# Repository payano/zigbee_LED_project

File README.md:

# zigbee_LED_project

Inspiration:
https://arduinodiy.wordpress.com/2012/05/02/using-mosfets-with-ttl-levels/

this aswell: https://github.com/karlp/Mrf24j40-arduino-library/

Potentiometer
BC547
IRF3205
LED-panel (aliexpress)
RGBW-led strips (aliexpress)

THIS TOO: https://electronics.stackexchange.com/questions/132000/stm32-series-microcontroller-calculations-of-timer-variables

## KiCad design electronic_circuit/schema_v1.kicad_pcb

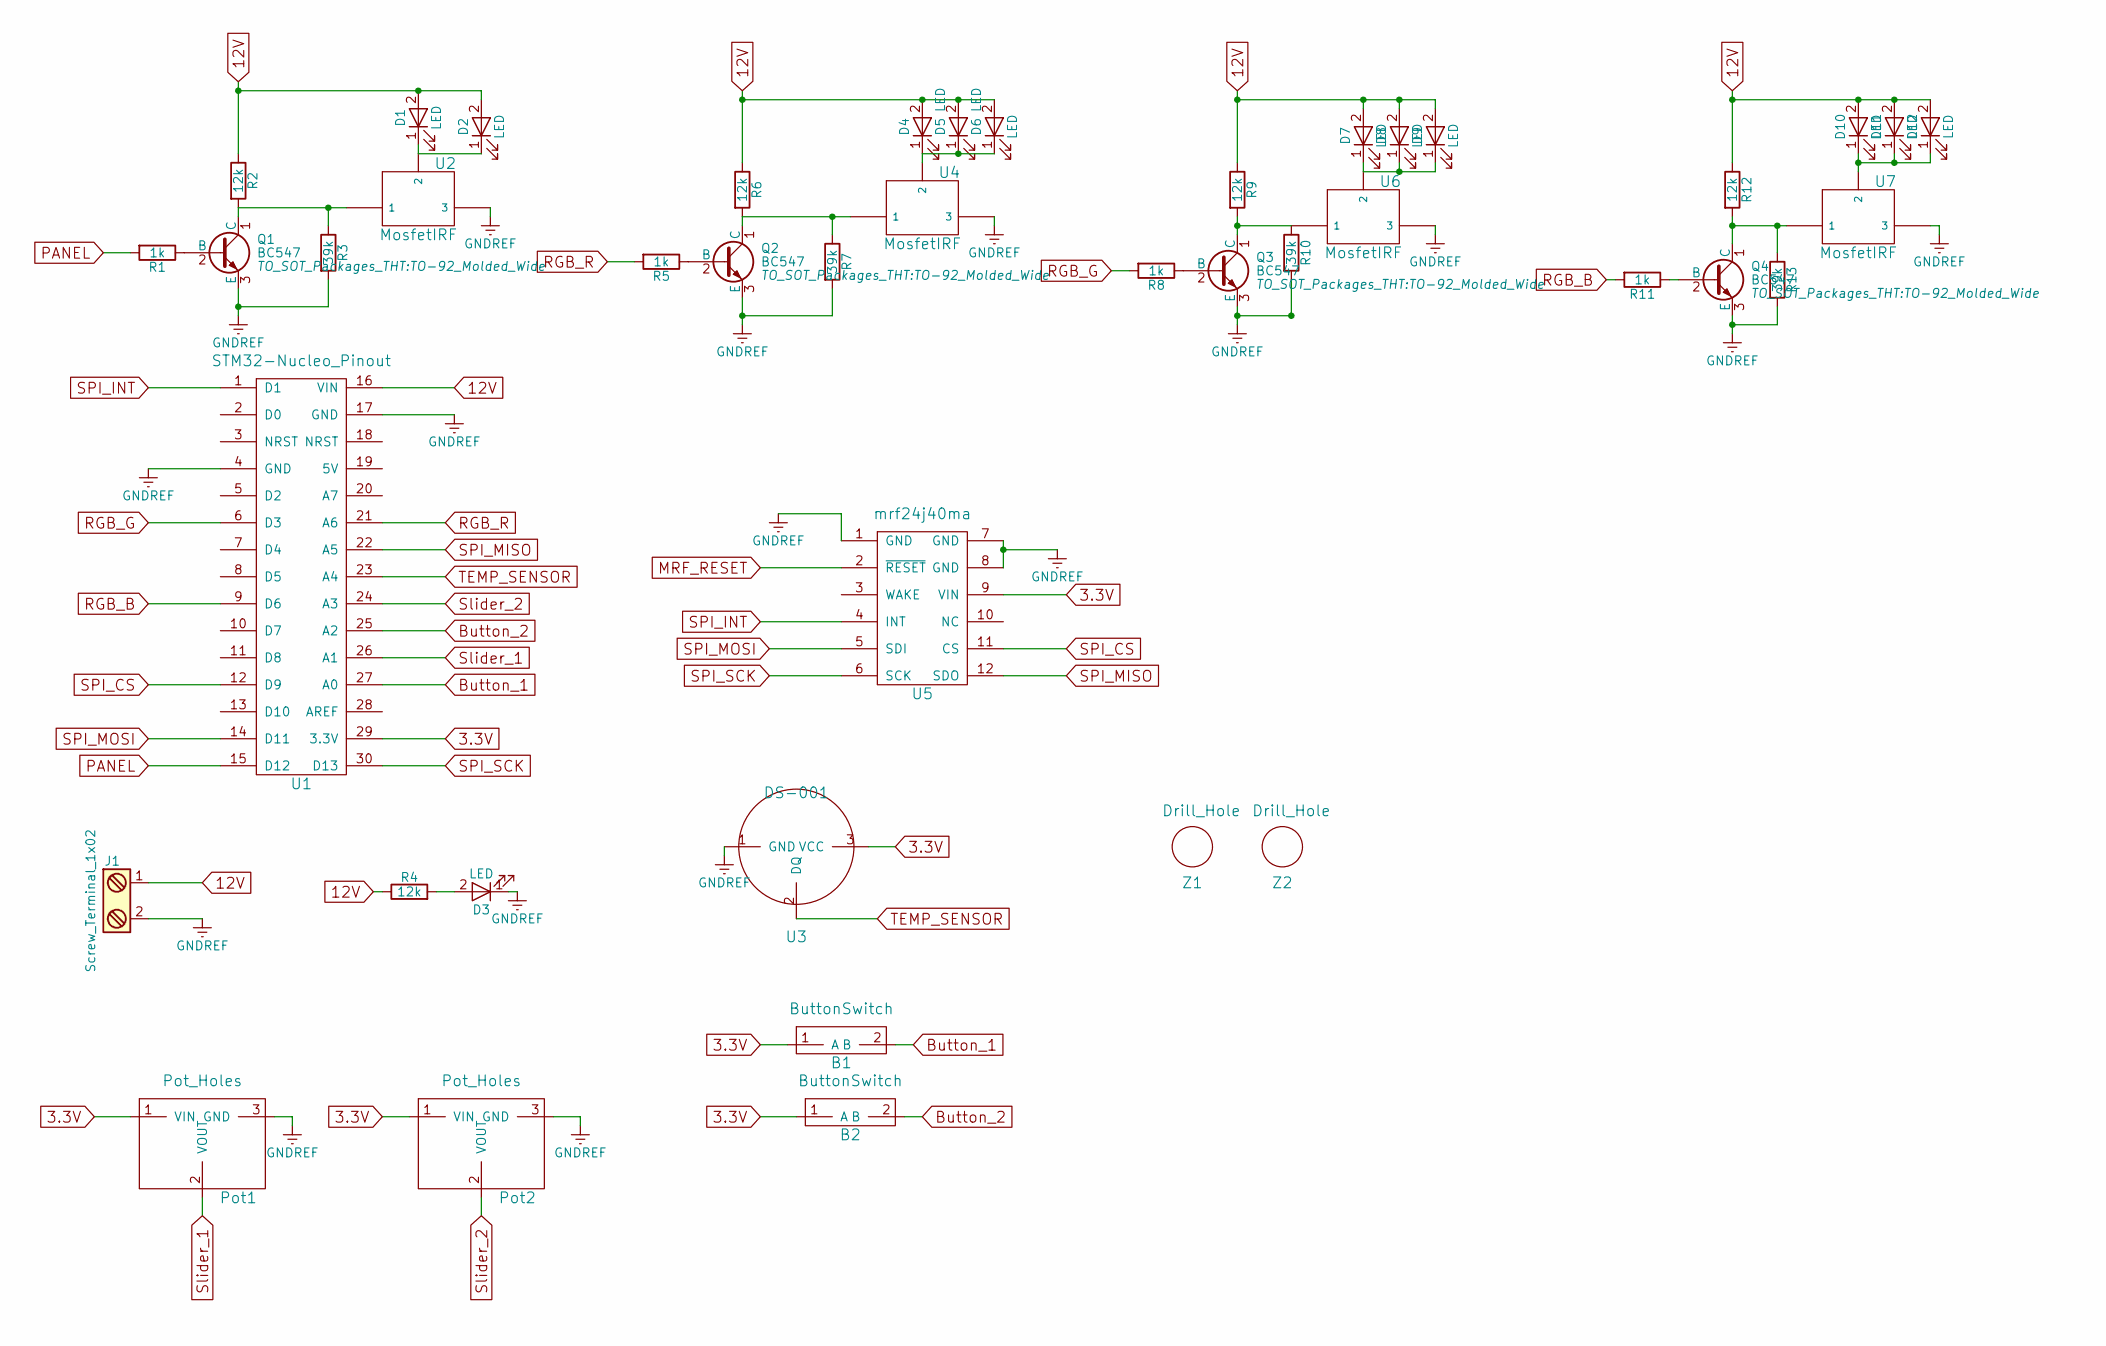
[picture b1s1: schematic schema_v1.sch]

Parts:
B1, B2: ButtonSwitch
D1, D2, D3, D4, D5, D6, D7, D8, D9, D10, D11, D12: LED; LED-8MM
J1: Screw_Terminal_1x02; P_Led_Holes
Pot1, Pot2: Pot_Holes
Q1, Q2, Q3, Q4: BC547; TO-92_Molded_Wide
R1, R5, R8, R11: 1k; R_1206
R2, R4, R6, R9, R12: 12k; R_1206
R3, R7, R10, R13: 39k; R_1206
U1: STM32-Nucleo_Pinout
U2, U4, U6, U7: MosfetIRF; IRF3205
U3: DS-001; TO-92_Molded_Wide
U5: mrf24j40ma
Z1, Z2: Drill_Hole

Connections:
3.3V: B1.1 (A), B2.1 (A), Pot1.1 (VIN), Pot2.1 (VIN), U1.29 (3.3V), U3.3 (VCC), U5.9 (VIN)
12V: D1.2 (A), D2.2 (A), D4.2 (A), D5.2 (A), D6.2 (A), D7.2 (A), D8.2 (A), D9.2 (A), D10.2 (A), D11.2 (A), D12.2 (A), J1.1, R2.1, R4.1, R6.1, R9.1, R12.1, U1.16 (VIN)
Button_1: B1.2 (B), U1.27 (A0)
Button_2: B2.2 (B), U1.25 (A2)
GNDREF: D3.1 (K), J1.2, Pot1.3 (GND), Pot2.3 (GND), Q1.3 (E), Q2.3 (E), Q3.3 (E), Q4.3 (E), R3.2, R7.2, R10.2, R13.2, U1.4 (GND), U1.17 (GND), U2.3, U3.1 (GND), U4.3, U5.1 (GND), U5.7 (GND), U5.8 (GND), U6.3, U7.3
MRF_RESET: U5.2 (~RESET)
unnamed: D1.1 (K), D2.1 (K), U2.2
unnamed: D3.2 (A), R4.2
unnamed: D4.1 (K), D5.1 (K), D6.1 (K), U4.2
unnamed: D7.1 (K), D8.1 (K), D9.1 (K), U6.2
unnamed: D10.1 (K), D11.1 (K), D12.1 (K), U7.2
unnamed: Q1.1 (C), R2.2, R3.1, U2.1
unnamed: Q1.2 (B), R1.1
unnamed: Q2.1 (C), R6.2, R7.1, U4.1
unnamed: Q2.2 (B), R5.1
unnamed: Q3.1 (C), R9.2, R10.1, U6.1
unnamed: Q3.2 (B), R8.1
unnamed: Q4.1 (C), R12.2, R13.1, U7.1
unnamed: Q4.2 (B), R11.1
PANEL: R1.2, U1.15 (D12)
RGB_B: R11.2, U1.9 (D6)
RGB_G: R8.2, U1.6 (D3)
RGB_R: R5.2, U1.21 (A6)
SPI_CS: U1.12 (D9), U5.11 (CS)
SPI_INT: U1.1 (D1), U5.4 (INT)
SPI_MISO: U1.22 (A5), U5.12 (SDO)
SPI_MOSI: U1.14 (D11), U5.5 (SDI)
SPI_SCK: U1.30 (D13), U5.6 (SCK)
Slider_1: Pot1.2 (VOUT), U1.26 (A1)
Slider_2: Pot2.2 (VOUT), U1.24 (A3)
TEMP_SENSOR: U1.23 (A4), U3.2 (DQ)

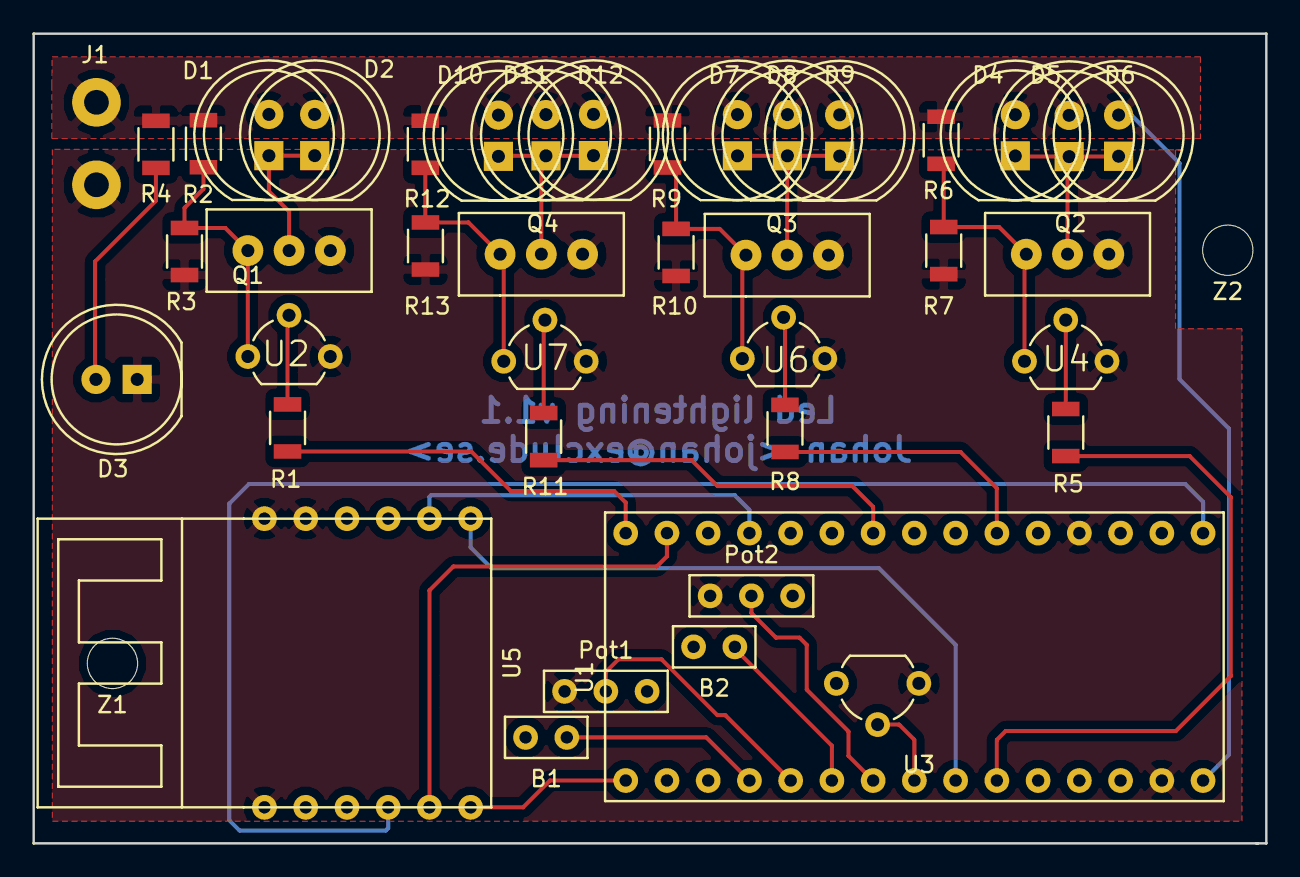
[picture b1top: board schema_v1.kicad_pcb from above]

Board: 2 copper layers, 75.9 x 49.9 mm, 43 parts (0 on the bottom side), 30 nets.

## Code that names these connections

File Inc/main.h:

/**
  ******************************************************************************
  * @file           : main.h
  * @brief          : Header for main.c file.
  *                   This file contains the common defines of the application.
  ******************************************************************************
  ** This notice applies to any and all portions of this file
  * that are not between comment pairs USER CODE BEGIN and
  * USER CODE END. Other portions of this file, whether 
  * inserted by the user or by software development tools
  * are owned by their respective copyright owners.
  *
  * COPYRIGHT(c) 2018 STMicroelectronics
  *
  * Redistribution and use in source and binary forms, with or without modification,
  * are permitted provided that the following conditions are met:
  *   1. Redistributions of source code must retain the above copyright notice,
  *      this list of conditions and the following disclaimer.
  *   2. Redistributions in binary form must reproduce the above copyright notice,
  *      this list of conditions and the following disclaimer in the documentation
  *      and/or other materials provided with the distribution.
  *   3. Neither the name of STMicroelectronics nor the names of its contributors
  *      may be used to endorse or promote products derived from this software
  *      without specific prior written permission.
  *
  * THIS SOFTWARE IS PROVIDED BY THE COPYRIGHT HOLDERS AND CONTRIBUTORS "AS IS"
  * AND ANY EXPRESS OR IMPLIED WARRANTIES, INCLUDING, BUT NOT LIMITED TO, THE
  * IMPLIED WARRANTIES OF MERCHANTABILITY AND FITNESS FOR A PARTICULAR PURPOSE ARE
  * DISCLAIMED. IN NO EVENT SHALL THE COPYRIGHT HOLDER OR CONTRIBUTORS BE LIABLE
  * FOR ANY DIRECT, INDIRECT, INCIDENTAL, SPECIAL, EXEMPLARY, OR CONSEQUENTIAL
  * DAMAGES (INCLUDING, BUT NOT LIMITED TO, PROCUREMENT OF SUBSTITUTE GOODS OR
  * SERVICES; LOSS OF USE, DATA, OR PROFITS; OR BUSINESS INTERRUPTION) HOWEVER
  * CAUSED AND ON ANY THEORY OF LIABILITY, WHETHER IN CONTRACT, STRICT LIABILITY,
  * OR TORT (INCLUDING NEGLIGENCE OR OTHERWISE) ARISING IN ANY WAY OUT OF THE USE
  * OF THIS SOFTWARE, EVEN IF ADVISED OF THE POSSIBILITY OF SUCH DAMAGE.
  *
  ******************************************************************************
  */

/* Define to prevent recursive inclusion -------------------------------------*/
#ifndef __MAIN_H__
#define __MAIN_H__

/* Includes ------------------------------------------------------------------*/

/* USER CODE BEGIN Includes */

/* USER CODE END Includes */

/* Private define ------------------------------------------------------------*/

#define BUTTON_1_Pin GPIO_PIN_0
#define BUTTON_1_GPIO_Port GPIOA
#define BUTTON_1_EXTI_IRQn EXTI0_1_IRQn
#define SLIDER_1_Pin GPIO_PIN_1
#define SLIDER_1_GPIO_Port GPIOA
#define VCP_TX_Pin GPIO_PIN_2
#define VCP_TX_GPIO_Port GPIOA
#define BUTTON_2_Pin GPIO_PIN_3
#define BUTTON_2_GPIO_Port GPIOA
#define BUTTON_2_EXTI_IRQn EXTI2_3_IRQn
#define SLIDER_2_Pin GPIO_PIN_4
#define SLIDER_2_GPIO_Port GPIOA
#define TEMP_SENSOR_Pin GPIO_PIN_5
#define TEMP_SENSOR_GPIO_Port GPIOA
#define SPI_MISO_Pin GPIO_PIN_6
#define SPI_MISO_GPIO_Port GPIOA
#define LED_PANEL_Pin GPIO_PIN_7
#define LED_PANEL_GPIO_Port GPIOA
#define RGB_R_Pin GPIO_PIN_0
#define RGB_R_GPIO_Port GPIOB
#define RGB_G_Pin GPIO_PIN_1
#define RGB_G_GPIO_Port GPIOB
#define SPI_CS_Pin GPIO_PIN_8
#define SPI_CS_GPIO_Port GPIOA
#define SPI_INT_Pin GPIO_PIN_9
#define SPI_INT_GPIO_Port GPIOA
#define SPI_INT_EXTI_IRQn EXTI4_15_IRQn
#define SWDIO_Pin GPIO_PIN_13
#define SWDIO_GPIO_Port GPIOA
#define SWCLK_Pin GPIO_PIN_14
#define SWCLK_GPIO_Port GPIOA
#define VCP_RX_Pin GPIO_PIN_15
#define VCP_RX_GPIO_Port GPIOA
#define SPI_SCK_Pin GPIO_PIN_3
#define SPI_SCK_GPIO_Port GPIOB
#define RGB_B_Pin GPIO_PIN_4
#define RGB_B_GPIO_Port GPIOB
#define SPI_MOSI_Pin GPIO_PIN_5
#define SPI_MOSI_GPIO_Port GPIOB
#define MRF_RESET_Pin GPIO_PIN_6
#define MRF_RESET_GPIO_Port GPIOB
#define MRF_WAKE_Pin GPIO_PIN_7
#define MRF_WAKE_GPIO_Port GPIOB

/* ########################## Assert Selection ############################## */
/**
  * @brief Uncomment the line below to expanse the "assert_param" macro in the 
  *        HAL drivers code
  */
/* #define USE_FULL_ASSERT    1U */

/* USER CODE BEGIN Private defines */

/* USER CODE END Private defines */

#ifdef __cplusplus
 extern "C" {
#endif
void _Error_Handler(char *, int);

#define Error_Handler() _Error_Handler(__FILE__, __LINE__)
#ifdef __cplusplus
}
#endif

#endif /* __MAIN_H__ */

/************************ (C) COPYRIGHT STMicroelectronics *****END OF FILE****/

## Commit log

2017-09-17 ignorefile and some stmcube32mx changes.
2017-09-19 updated flowchart
2017-09-21 removed FreeRTOS due to hardware limitations, Changed flowchart and class schema. Refactored code to not use FreeRTOS.
2017-09-21 added eclipse warnings to errors! Updated flowchart
2017-09-21 updated svg file
2017-09-22 working on handlers.
2017-09-22 successfully send message between classes.
2017-09-22 interrupts working.
2017-09-23 fixed ADC DMA and button interrupts
2017-09-23 reworked main
2017-09-23 some docs added
2017-09-25 added a interrupthandler, also refactored some.
2017-09-25 Removed vector and added an array instead.
2017-09-26 Renamed InterruptHandler to HalHandler, and also did some refactoring.
2017-09-26 more work
2017-09-27 more work towrads halhandler.
2017-09-30 working on HalHandler.
2017-09-30 HalHandler and LedHandler has a working concept.
2017-09-30 Buttonhandler is tricky.
2017-10-01 refactored message class.
2017-10-03 Got stuck in a infinite loop, when std::queue got removed it worked better.
2017-10-05 Created an own message system.
2017-10-06 buttons and led almost done.
2017-10-07 Working prototype.
2017-10-07 Reworked flowchart.
2017-10-07 timer calc
2017-10-08 Imported MRF24j from github
2017-10-15 Added pull up on PWM.
2017-10-15 Added pulldown on buttons
2017-10-15 range to highest and lowest value.. Might a const instead?
2017-10-18 A layout circuit diagram made in kicad.
2017-10-30 New electronic schema
2017-10-31 mapped channels to right output on the PCB.
2017-11-04 changed bouncing on button and that the pot could not set the brightness to 0 (254).
2017-12-01 Issue 1: Remapped Pot1 -> B1 and Pot2 > B2
2017-12-01 Issue 2: PWM changed to 10Khz.
2017-12-02 Issue 6: Lowered PWM output speed, Issue 2: Also made changes to STM32CubeMX
2017-12-04 Issue 2: PWM speed is now 31khz
2017-12-04 Issue 4: Created a start issue for all classes
2017-12-04 More sensitive pot
2017-12-06 Issue 5: Added a filter that removes the first interrupt
2017-12-06 Issue 5: Also made sure that the filter only applies on HAL messages.
2017-12-20 Issue 5: A new implementation of the bouncing problem.
2017-12-20 Lowered pwm to 10khz.
2017-12-20 Tried some combinations that seem to work for the bouncing
2018-02-22 some minor work
2018-02-23 radio works
2018-02-24 small steps
2018-02-25 More radio
2018-07-23 working with radio
2018-07-23 working prototype with rgb
2018-07-24 more work on radio, button bouncing is fixed.
2018-08-09 more improvements
2018-08-18 almost done with radio implementation
2018-08-18 done!
2018-08-18 minor change
2018-09-25 Now enables the interrupt at the last row in the interrupt routine.
2018-09-28 Revert "Now enables the interrupt at the last row in the interrupt routine."
    This reverts commit 2f00c25a86d0ec09e644e9e87e42694efe517a78.
2018-09-28 shortened the delay of the main loop
